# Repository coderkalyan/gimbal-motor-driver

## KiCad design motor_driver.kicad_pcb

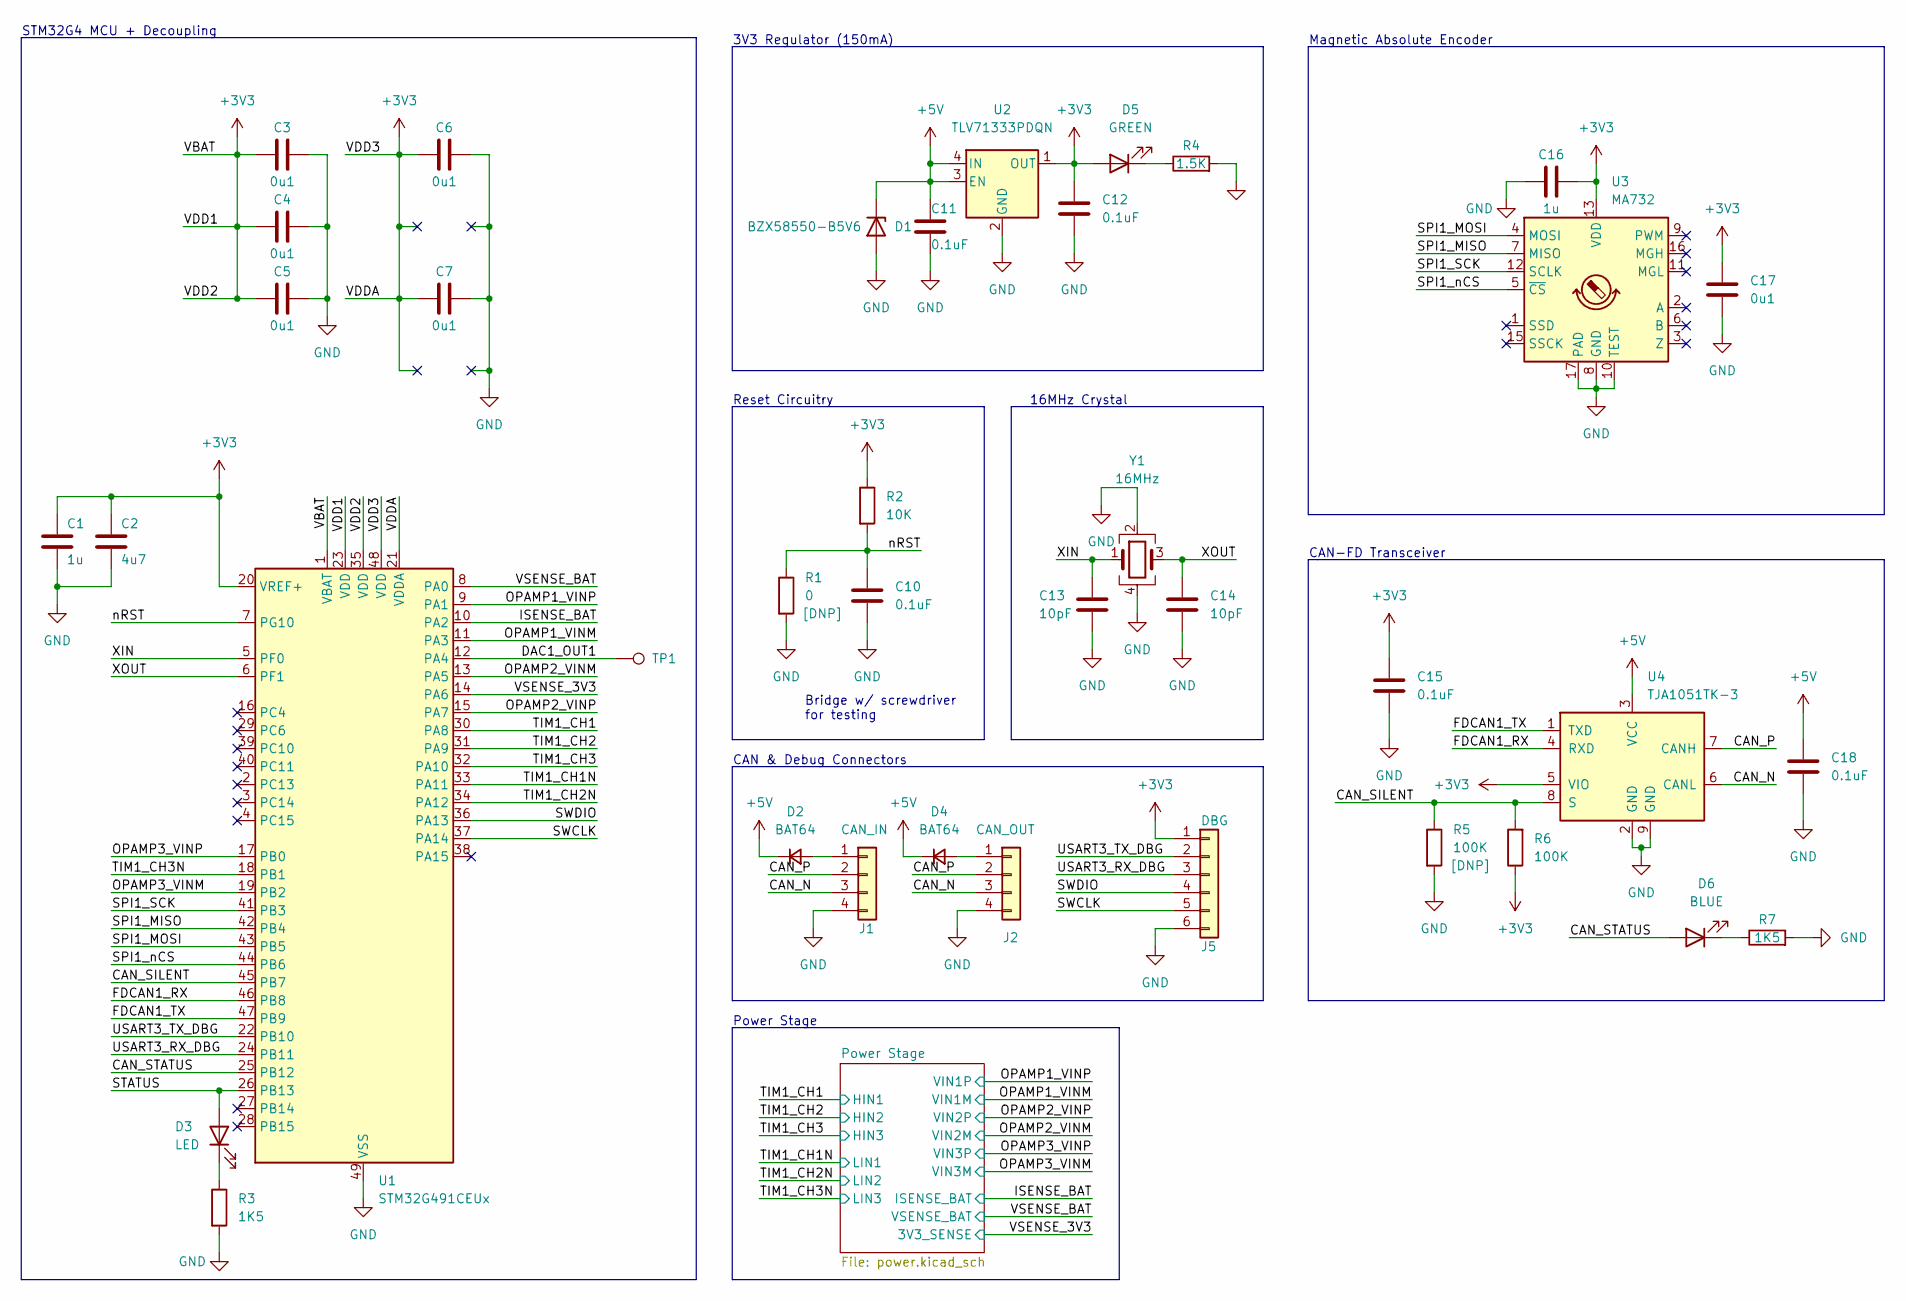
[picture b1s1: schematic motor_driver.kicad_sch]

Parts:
C1, C16: 1u; C_0402_1005Metric
C2: 4u7; C_0402_1005Metric
C3, C4, C5, C6, C7, C17: 0u1; C_0402_1005Metric
C10, C15, C18: 0.1uF; C_0402_1005Metric
C11, C12: 0.1uF; C_0603_1608Metric
C13, C14: 10pF; C_0402_1005Metric
D1: BZX58550-B5V6; D_SOD-523
D2, D4: BAT64; D_SOD-523
D3: LED; LED_0402_1005Metric
D5: GREEN; LED_0402_1005Metric; Part QBLP595-IG
D6: BLUE; LED_0402_1005Metric
J1: CAN_IN; JST_GH_SM04B-GHS-TB_1x04-1MP_P1.25mm_Horizontal
J2: CAN_OUT; JST_GH_SM04B-GHS-TB_1x04-1MP_P1.25mm_Horizontal
J5: DBG; JST_GH_SM06B-GHS-TB_1x06-1MP_P1.25mm_Horizontal
R1: 0; R_0402_1005Metric
R2: 10K; R_0402_1005Metric
R3, R7: 1K5; R_0402_1005Metric
R4: 1.5K; R_0402_1005Metric
R5, R6: 100K; R_0402_1005Metric
TP1: TestPoint; TestPoint_Pad_1.0x1.0mm
U1: STM32G491CEUx; QFN-48-1EP_7x7mm_P0.5mm_EP5.6x5.6mm
U2: TLV71333PDQN; Texas_X2SON-4_1x1mm_P0.65mm
U3: MA732; QFN-16-1EP_3x3mm_P0.5mm_EP1.7x1.7mm
U4: TJA1051TK-3; DFN-8-1EP_3x3mm_P0.65mm_EP1.55x2.4mm
Y1: 16MHz; Crystal_SMD_2520-4Pin_2.5x2.0mm; Part R2520-12.000-10-3030-TR

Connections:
+3V3: C1.1, C2.1, C3.1, C4.1, C5.1, C6.1, C7.1, C12.1, C15.1, C16.2, C17.1, D5.2 (A), J5.1, R2.1, R6.1, U1.1 (VBAT), U1.20 (VREF+), U1.21 (VDDA), U1.23 (VDD), U1.35 (VDD), U1.48 (VDD), U2.1 (OUT), U3.13 (VDD), U4.5 (VIO); also elsewhere on the board
+5V: C11.1, C18.1, D1.1 (K), D2.1 (K), D4.1 (K), U2.3 (EN), U2.4 (IN), U4.3 (VCC)
/CAN_N: J1.3, J2.3, U4.6 (CANL)
/CAN_P: J1.2, J2.2, U4.7 (CANH)
/CAN_SILENT: R5.1, R6.2, U1.45 (PB7), U4.8 (S)
/CAN_STATUS: D6.2 (A), U1.25 (PB12)
/DAC1_OUT1: TP1.1, U1.12 (PA4)
/FDCAN1_RX: U1.46 (PB8), U4.4 (RXD)
/FDCAN1_TX: U1.47 (PB9), U4.1 (TXD)
/ISENSE_BAT: U1.10 (PA2); also elsewhere on the board
/OPAMP1_VINM: U1.11 (PA3); also elsewhere on the board
/OPAMP1_VINP: U1.9 (PA1); also elsewhere on the board
/OPAMP2_VINM: U1.13 (PA5); also elsewhere on the board
/OPAMP2_VINP: U1.15 (PA7); also elsewhere on the board
/OPAMP3_VINM: U1.19 (PB2); also elsewhere on the board
/OPAMP3_VINP: U1.17 (PB0); also elsewhere on the board
/SPI1_MISO: U1.42 (PB4), U3.7 (MISO)
/SPI1_MOSI: U1.43 (PB5), U3.4 (MOSI)
/SPI1_SCK: U1.41 (PB3), U3.12 (SCLK)
/SPI1_nCS: U1.44 (PB6), U3.5 (~CS)
/STATUS: D3.2 (A), U1.26 (PB13)
/SWCLK: J5.5, U1.37 (PA14)
/SWDIO: J5.4, U1.36 (PA13)
/TIM1_CH1: U1.30 (PA8); also elsewhere on the board
/TIM1_CH1N: U1.33 (PA11); also elsewhere on the board
/TIM1_CH2: U1.31 (PA9); also elsewhere on the board
/TIM1_CH2N: U1.34 (PA12); also elsewhere on the board
/TIM1_CH3: U1.32 (PA10); also elsewhere on the board
/TIM1_CH3N: U1.18 (PB1); also elsewhere on the board
/USART3_RX_DBG: J5.3, U1.24 (PB11)
/USART3_TX_DBG: J5.2, U1.22 (PB10)
/VSENSE_3V3: U1.14 (PA6); also elsewhere on the board
/VSENSE_BAT: U1.8 (PA0); also elsewhere on the board
/XIN: C13.1, U1.5 (PF0), Y1.1
/XOUT: C14.1, U1.6 (PF1), Y1.3
/nRST: C10.1, R1.1, R2.2, U1.7 (PG10)
unnamed: D2.2 (A), J1.1
unnamed: D3.1 (K), R3.1
unnamed: D4.2 (A), J2.1
unnamed: D5.1 (K), R4.1
unnamed: D6.1 (K), R7.1

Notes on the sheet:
Magnetic Absolute Encoder
STM32G4 MCU + Decoupling
3V3 Regulator (150mA)
Bridge w/ screwdriver for testing
Power Stage
CAN-FD Transceiver
16MHz Crystal
Reset Circuitry
CAN & Debug Connectors

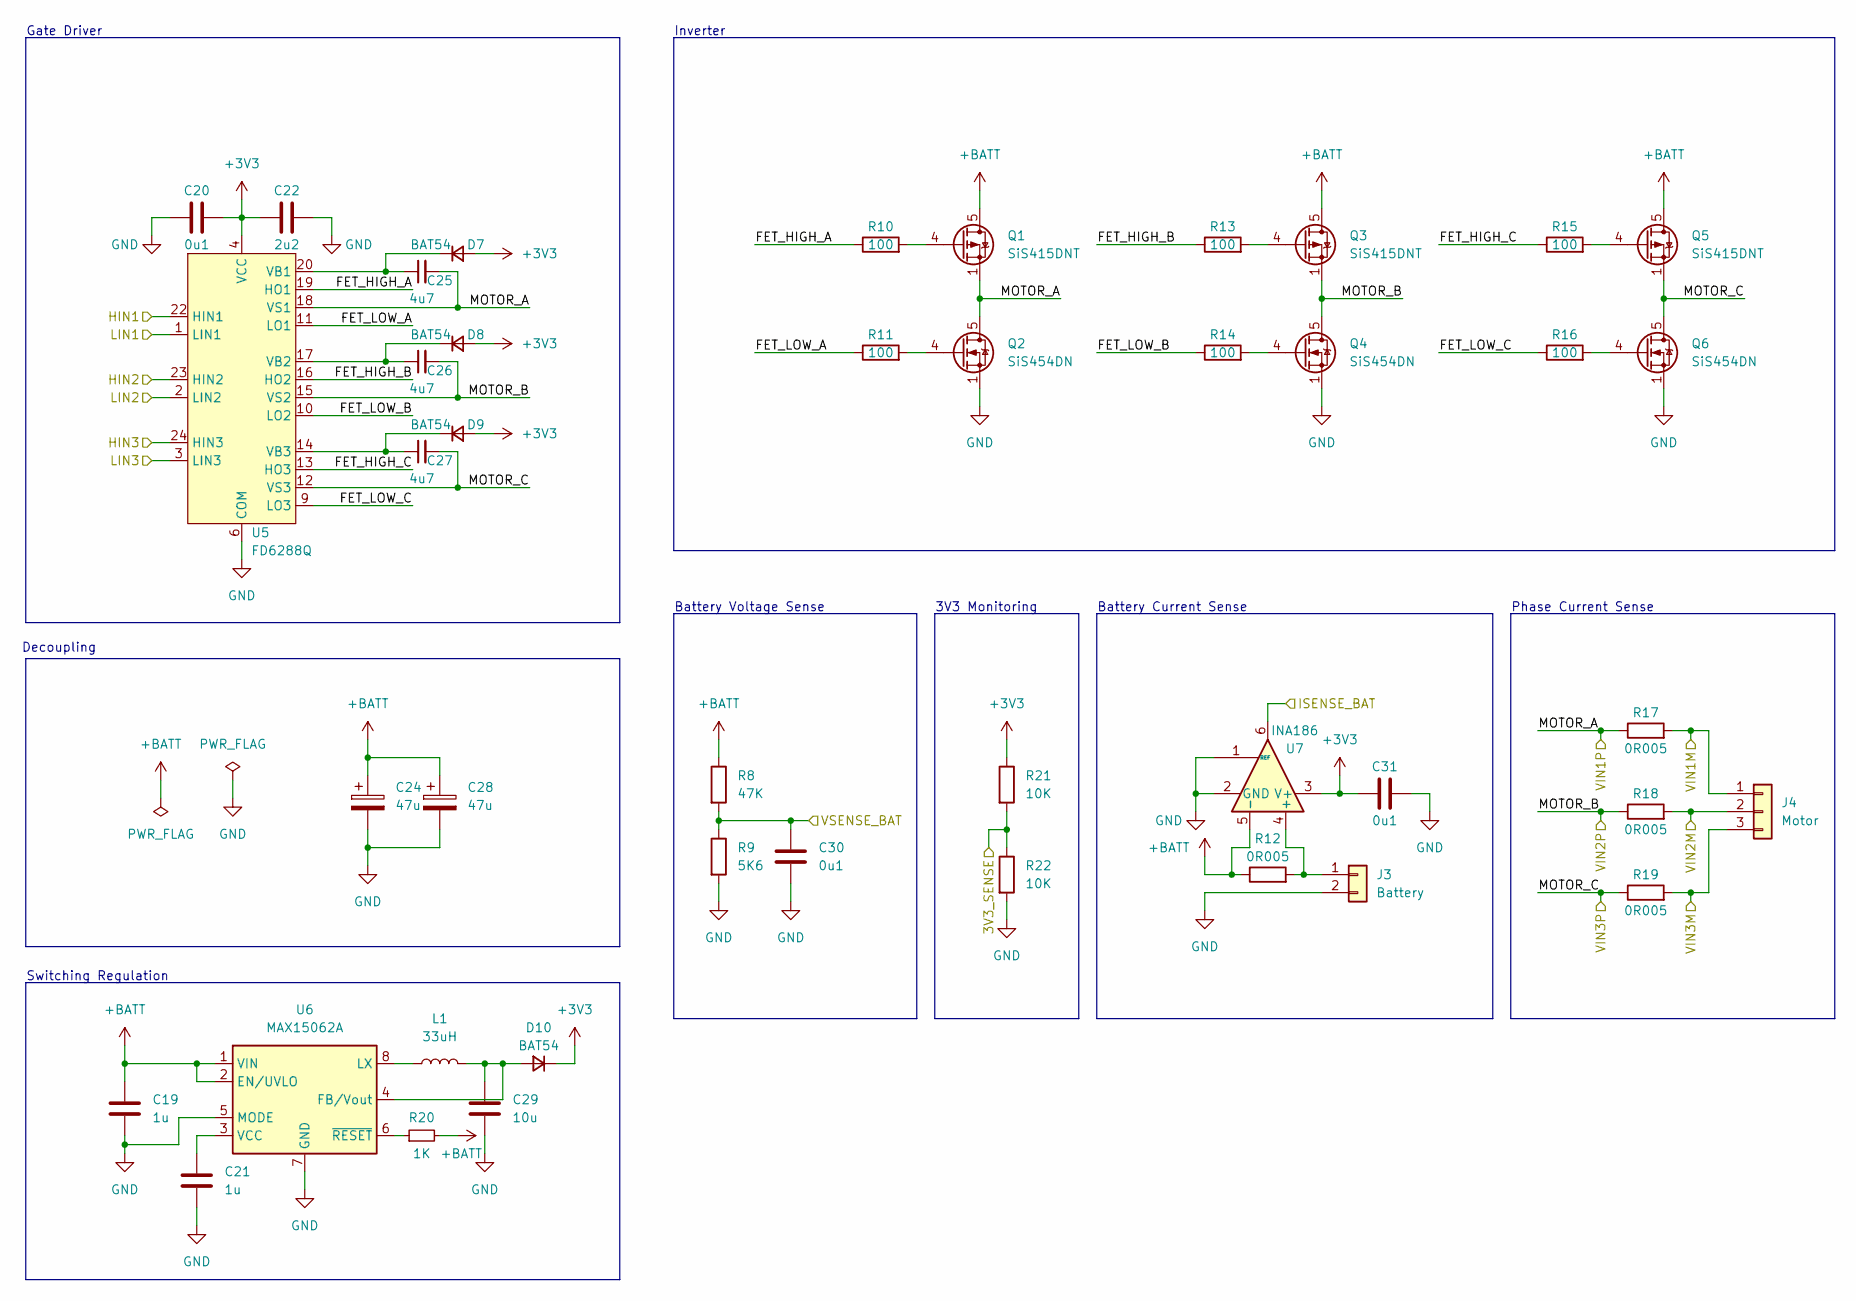
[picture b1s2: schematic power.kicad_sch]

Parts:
C19: 1u; C_0805_2012Metric
C20, C30, C31: 0u1; C_0402_1005Metric
C21: 1u; C_0603_1608Metric
C22: 2u2; C_0402_1005Metric
C24, C28: 47u; C_1206_3216Metric
C25, C26, C27: 4u7; C_0402_1005Metric
C29: 10u; C_0603_1608Metric
D7, D8, D9: BAT54; D_SOD-723
D10: BAT54; D_SOD-523
J3: Battery; Molex_Micro-Fit_3.0_43650-0200_1x02_P3.00mm_Horizontal
J4: Motor; Molex_Micro-Fit_3.0_43650-0300_1x03_P3.00mm_Horizontal
L1: 33uH; L_1210_3225Metric
Q1, Q3, Q5: SiS415DNT; Vishay_PowerPAK_1212-8_Single
Q2, Q4, Q6: SiS454DN; Vishay_PowerPAK_1212-8_Single
R8: 47K; R_0402_1005Metric
R9: 5K6; R_0402_1005Metric
R10, R11, R13, R14, R15, R16: 100; R_0402_1005Metric
R12, R17, R18, R19: 0R005; R_1210_3225Metric
R20: 1K; R_0402_1005Metric
R21, R22: 10K; R_0402_1005Metric
U5: FD6288Q; QFN-24-1EP_4x4mm_P0.5mm_EP2.7x2.7mm
U6: MAX15062A; DFN-8_2x2mm_P0.5mm
U7: INA186; SOT-23-6

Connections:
+3V3: C20.2, C22.1, C31.1, D7.2 (A), D8.2 (A), D9.2 (A), D10.1 (K), R21.1, U5.4 (VCC), U7.3 (V+); also elsewhere on the board
+BATT: C19.1, C24.1, C28.1, Q1.5 (D), Q3.5 (D), Q5.5 (D), R8.1, R12.1, R20.2, U6.1 (VIN), U6.2 (EN/UVLO), U7.5 (-)
/ISENSE_BAT: U7.6; also elsewhere on the board
/OPAMP1_VINM: J4.1, R17.2; also elsewhere on the board
/OPAMP1_VINP: C25.2, Q1.1 (S), Q1.2 (S), Q1.3 (S), Q2.5 (D), R17.1, U5.18 (VS1); also elsewhere on the board
/OPAMP2_VINM: J4.2, R18.2; also elsewhere on the board
/OPAMP2_VINP: C26.2, Q3.1 (S), Q3.2 (S), Q3.3 (S), Q4.5 (D), R18.1, U5.15 (VS2); also elsewhere on the board
/OPAMP3_VINM: J4.3, R19.2; also elsewhere on the board
/OPAMP3_VINP: C27.2, Q5.1 (S), Q5.2 (S), Q5.3 (S), Q6.5 (D), R19.1, U5.12 (VS3); also elsewhere on the board
/Power Stage/FET_HIGH_A: R10.1, U5.19 (HO1)
/Power Stage/FET_HIGH_B: R13.1, U5.16 (HO2)
/Power Stage/FET_HIGH_C: R15.1, U5.13 (HO3)
/Power Stage/FET_LOW_A: R11.1, U5.11 (LO1)
/Power Stage/FET_LOW_B: R14.1, U5.10 (LO2)
/Power Stage/FET_LOW_C: R16.1, U5.9 (LO3)
/TIM1_CH1: U5.22 (HIN1); also elsewhere on the board
/TIM1_CH1N: U5.1 (LIN1); also elsewhere on the board
/TIM1_CH2: U5.23 (HIN2); also elsewhere on the board
/TIM1_CH2N: U5.2 (LIN2); also elsewhere on the board
/TIM1_CH3: U5.24 (HIN3); also elsewhere on the board
/TIM1_CH3N: U5.3 (LIN3); also elsewhere on the board
/VSENSE_3V3: R21.2, R22.1; also elsewhere on the board
/VSENSE_BAT: C30.1, R8.2, R9.1; also elsewhere on the board
unnamed: C29.1, D10.2 (A), L1.2, U6.4 (FB/Vout)
unnamed: J3.1, R12.2, U7.4 (+)
unnamed: Q1.4 (G), R10.2
unnamed: Q2.4 (G), R11.2
unnamed: Q3.4 (G), R13.2
unnamed: Q4.4 (G), R14.2
unnamed: Q5.4 (G), R15.2
unnamed: Q6.4 (G), R16.2
unnamed: L1.1, U6.8 (LX)
unnamed: C21.1, U6.3 (VCC)
unnamed: R20.1, U6.6 (~RESET)

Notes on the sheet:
Decoupling
Phase Current Sense
Switching Regulation
Battery Current Sense
Battery Voltage Sense
Inverter
3V3 Monitoring
Gate Driver

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
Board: 2 copper layers, 81 parts (37 on the bottom side), 63 nets, no tracks yet.

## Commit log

2023-04-07 finish schematic draft, start layout
2023-04-07 finish layout
